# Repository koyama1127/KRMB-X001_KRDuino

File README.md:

ATMEGA-328Pを使用したArduinoUNO R3互換ボード  
USBシリアル系のみ省略  
USBシリアル使用時は別途USBシリアルモジュールもしくはKREB-X001を使用

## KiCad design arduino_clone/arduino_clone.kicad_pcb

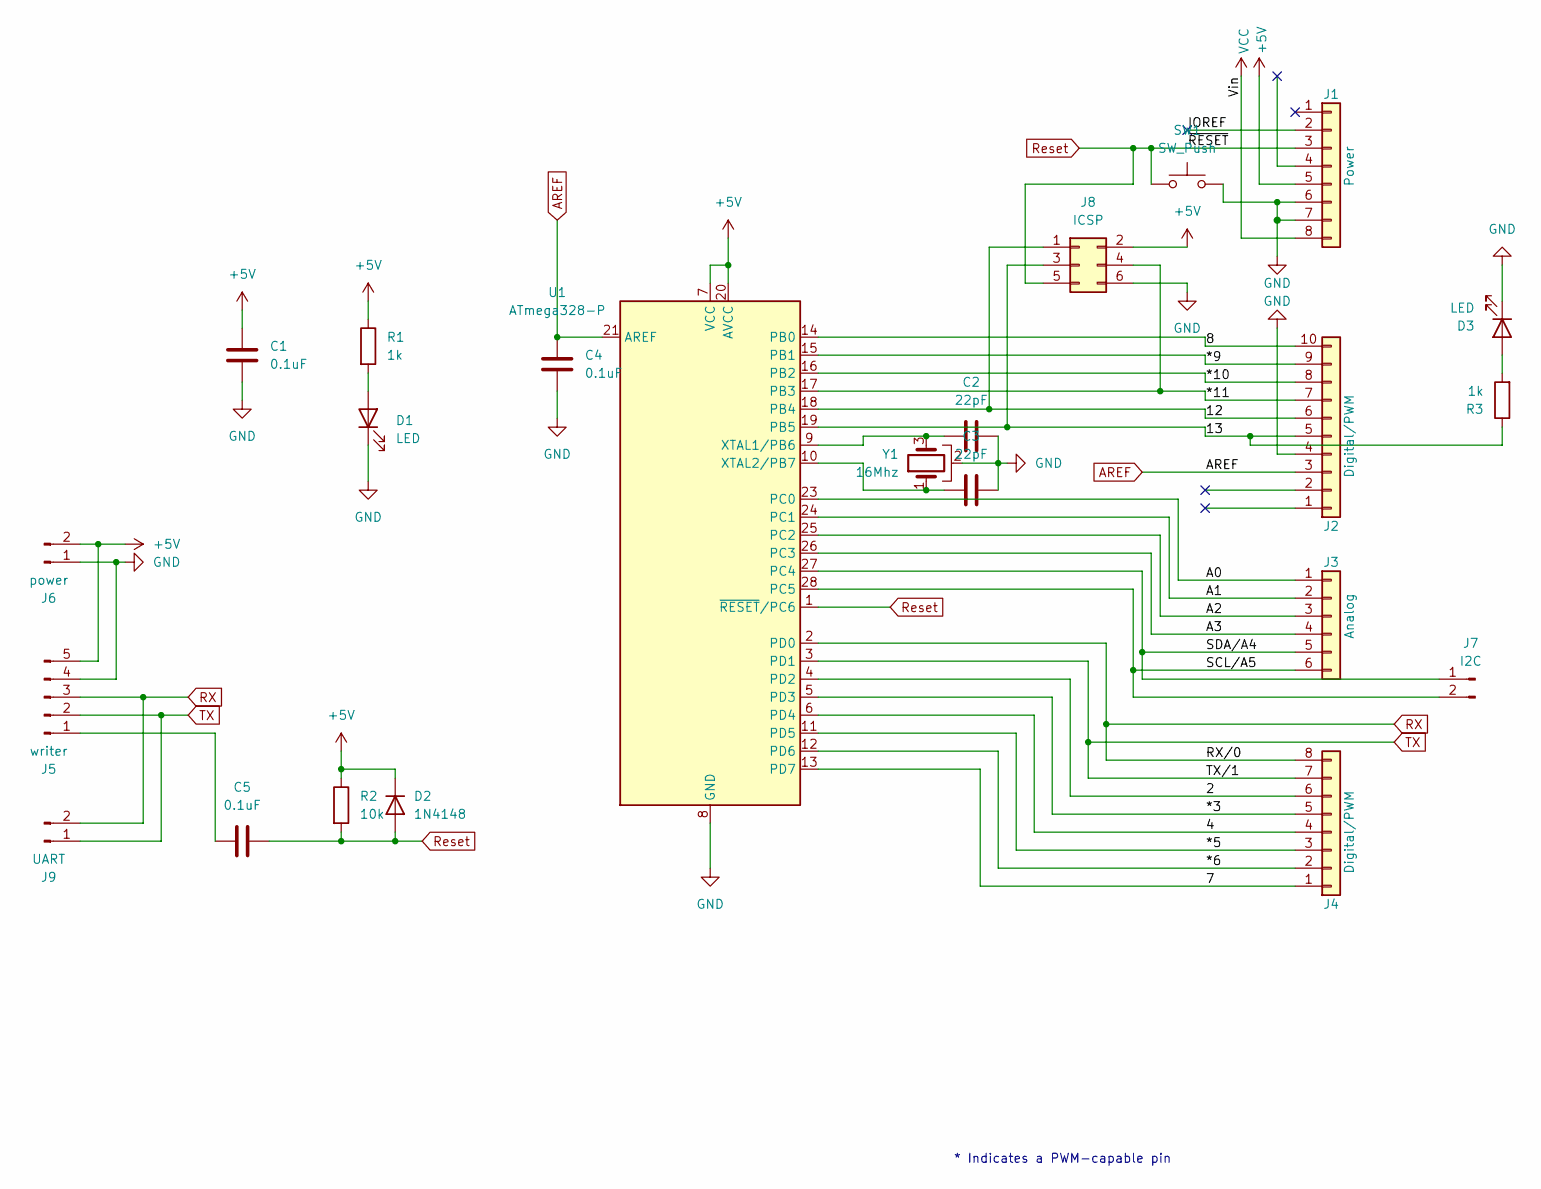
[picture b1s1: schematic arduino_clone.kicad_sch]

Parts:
C1, C4, C5: 0.1uF; C_Disc_D5.0mm_W2.5mm_P5.00mm
C2, C3: 22pF; C_Disc_D5.0mm_W2.5mm_P5.00mm
D1, D3: LED; LED_D3.0mm
D2: 1N4148; D_DO-35_SOD27_P7.62mm_Horizontal
J1: Power; PinSocket_1x08_P2.54mm_Vertical
J2: Digital/PWM; PinSocket_1x10_P2.54mm_Vertical
J3: Analog; PinSocket_1x06_P2.54mm_Vertical
J4: Digital/PWM; PinSocket_1x08_P2.54mm_Vertical
J5: writer; PinHeader_1x05_P2.54mm_Horizontal
J6: power; PinHeader_1x02_P2.54mm_Horizontal
J7: I2C; PinHeader_1x02_P2.54mm_Vertical
J8: ICSP; PinHeader_2x03_P2.54mm_Vertical
J9: UART; PinHeader_1x02_P2.54mm_Horizontal
R1, R3: 1k; R_Axial_DIN0204_L3.6mm_D1.6mm_P7.62mm_Horizontal
R2: 10k; R_Axial_DIN0204_L3.6mm_D1.6mm_P7.62mm_Horizontal
SW1: SW_Push; SW_PUSH_6mm_H7.3mm
U1: ATmega328-P; DIP-28_W7.62mm_Socket_LongPads
Y1: 16Mhz; Crystal_HC49-U-3Pin_Vertical

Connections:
+5V: C1.1, D2.1 (K), J1.5, J5.5, J6.2, J8.2, R1.1, R2.1, U1.7 (VCC), U1.20 (AVCC)
/2: J4.6, U1.4 (PD2)
/4: J4.4, U1.6 (PD4)
/7: J4.1, U1.13 (PD7)
/8: J2.10, U1.14 (PB0)
/12: J2.6, J8.1, U1.18 (PB4)
/13: J2.5, J8.3, R3.1, U1.19 (PB5)
/*3: J4.5, U1.5 (PD3)
/*5: J4.3, U1.11 (PD5)
/*6: J4.2, U1.12 (PD6)
/*9: J2.9, U1.15 (PB1)
/*10: J2.8, U1.16 (PB2)
/*11: J2.7, J8.4, U1.17 (PB3)
/A0: J3.1, U1.23 (PC0)
/A1: J3.2, U1.24 (PC1)
/A2: J3.3, U1.25 (PC2)
/A3: J3.4, U1.26 (PC3)
/IOREF: J1.2
/SCL/A5: J3.6, J7.2, U1.28 (PC5)
/SDA/A4: J3.5, J7.1, U1.27 (PC4)
AREF: C4.1, J2.3, U1.21 (AREF)
GND: C1.2, C2.2, C3.1, C4.2, D1.1 (K), D3.1 (K), J1.6, J1.7, J2.4, J5.4, J6.1, J8.6, SW1.2, U1.8 (GND), U1.22 (GND), Y1.2
unnamed: D1.2 (A), R1.2
unnamed: D3.2 (A), R3.2
unnamed: C5.1, J5.1
unnamed: C2.1, U1.9 (XTAL1/PB6), Y1.3
unnamed: C3.2, U1.10 (XTAL2/PB7), Y1.1
RX: J4.8, J5.3, J9.2, U1.2 (PD0)
Reset: C5.2, D2.2 (A), J1.3, J8.5, R2.2, SW1.1, U1.1 (~RESET/PC6)
TX: J4.7, J5.2, J9.1, U1.3 (PD1)
VCC: J1.8

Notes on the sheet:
* Indicates a PWM-capable pin

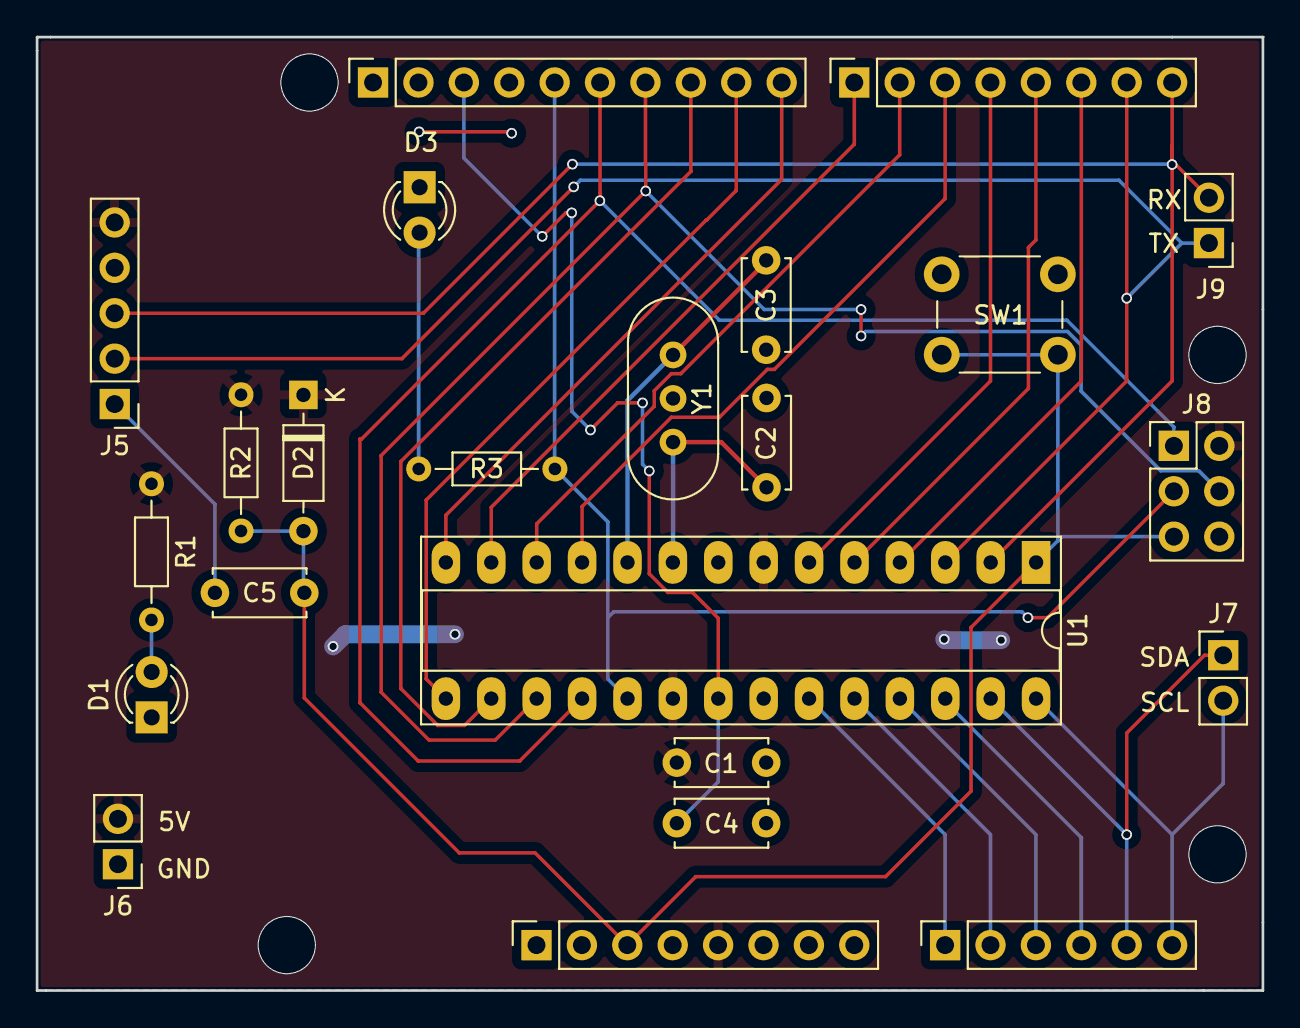
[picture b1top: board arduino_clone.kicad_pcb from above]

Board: 2 copper layers, 68.6 x 53.3 mm, 27 parts (0 on the bottom side), 29 nets.

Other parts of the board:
MH1, MH2, MH3, MH4: MountingHole_3.2mm

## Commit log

2025-02-06 試作ver0.1
